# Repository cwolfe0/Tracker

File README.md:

# SHC HAB Tracker
This is the Eagle schematic and board file for the Space Hardware Club HAB tracker.
It is capable of recording GPS, rotation data, pressure and temperature and sending the information via APRS and recording it to an SD card.

The board uses a:
- GPS
- Magnetometer
- MCU
- 5V Regulator
- 3.3V Regulator
- 2 Surefire C123A Batteries in series (6V, 3000mAh)
- APRS-capable Radio
- 2 Logic Gates (for allowing 5V input to the radio from the MCU)
- Pressure Sensor
- Slider Switch
- PDI Interface

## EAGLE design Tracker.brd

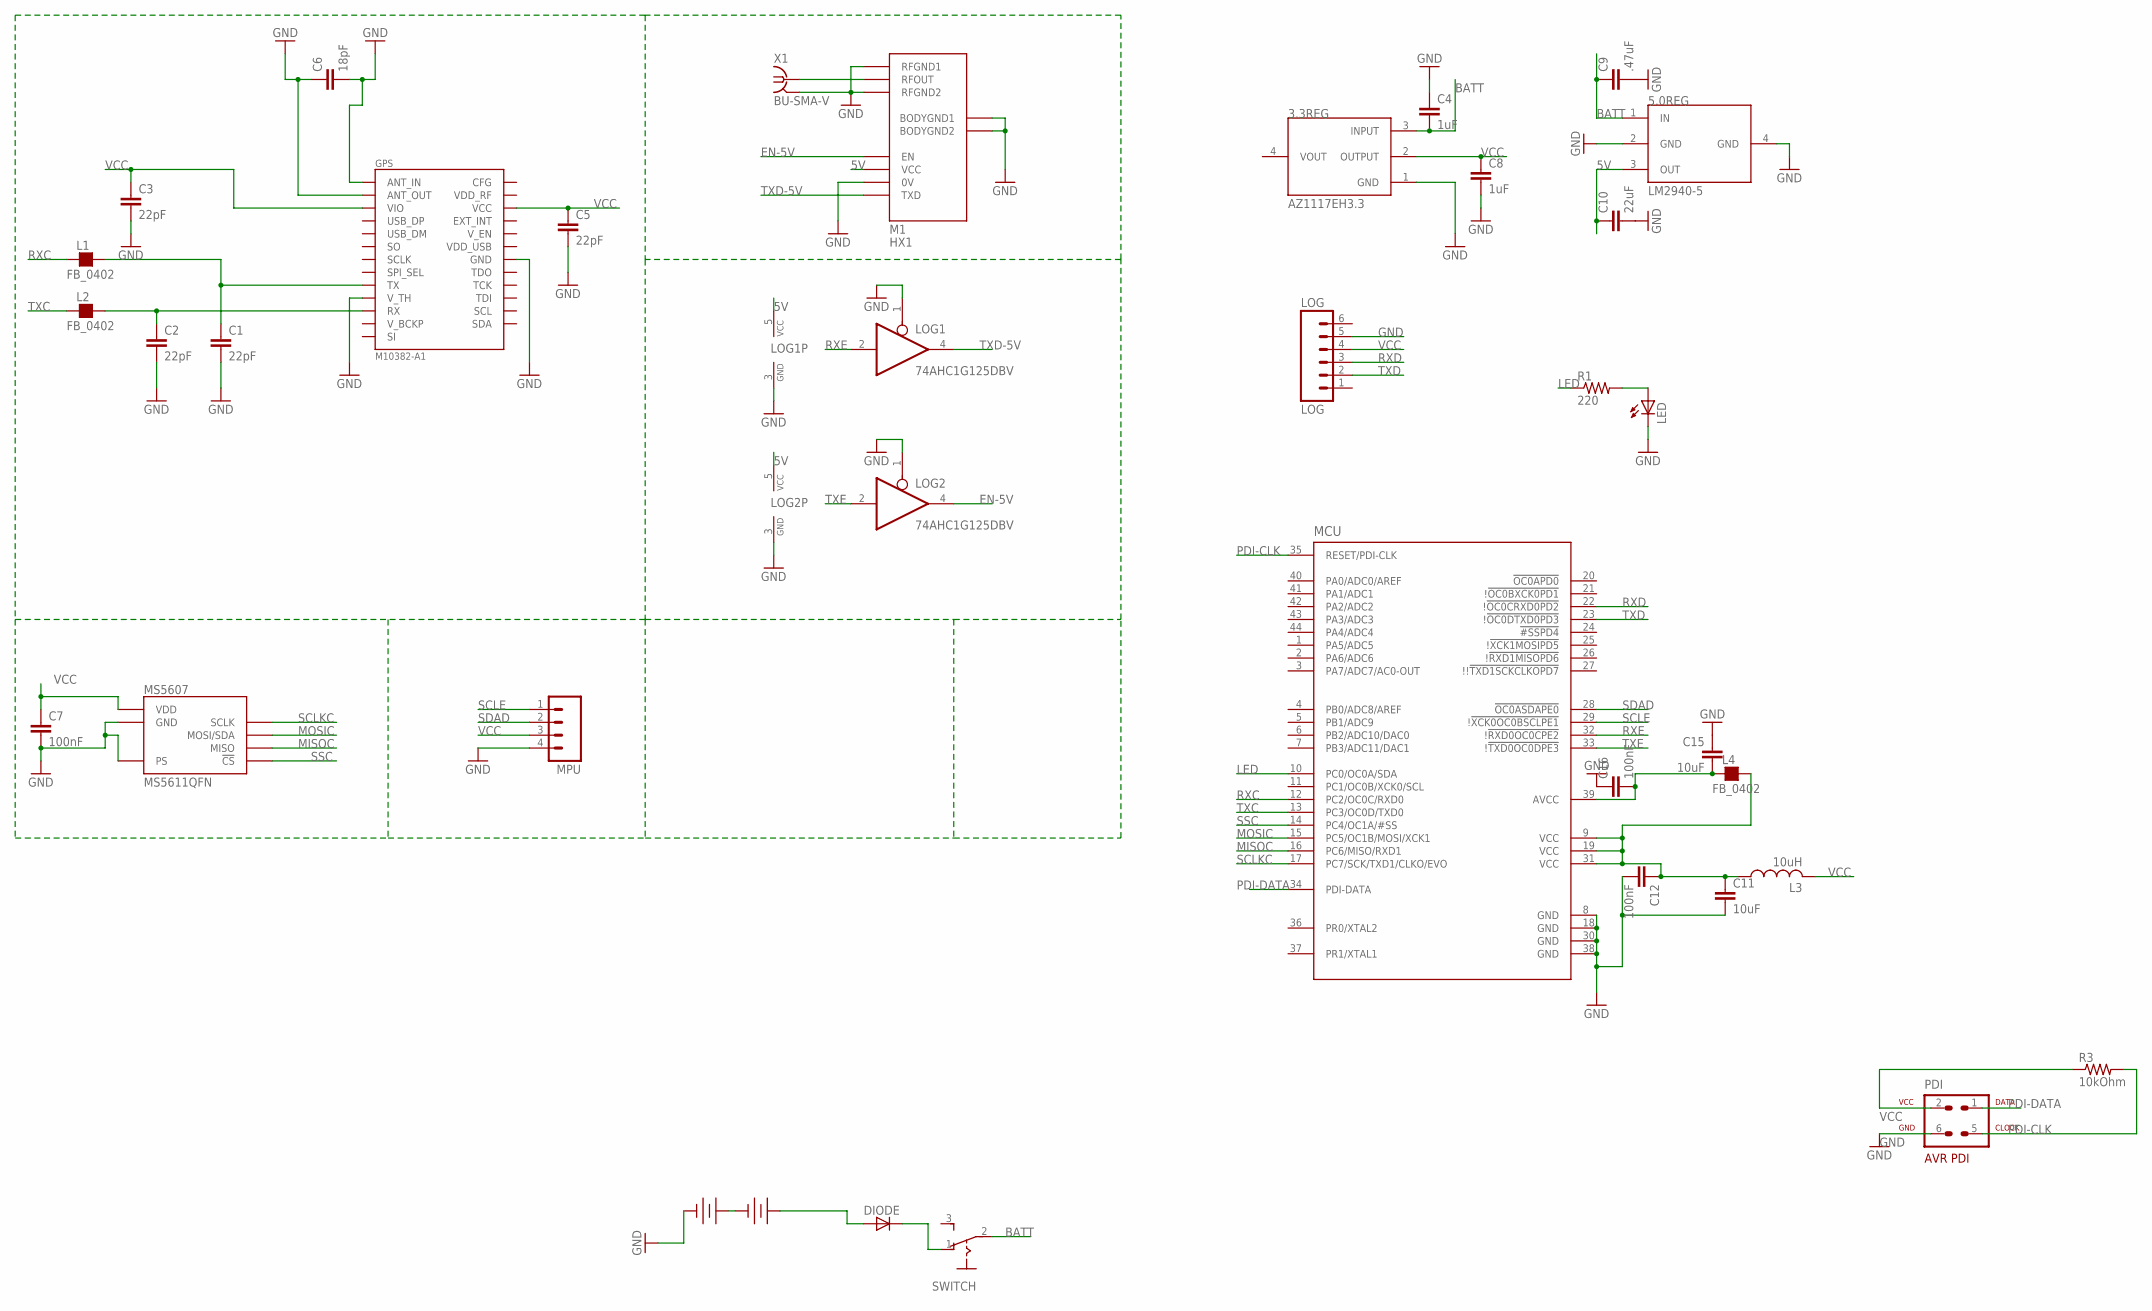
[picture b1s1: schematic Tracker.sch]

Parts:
3.3REG: AZ1117EH3.3; SOT-223
5.0REG: LM2940-5; SOT-223
BATT1, BATT2: 123_BATTERY_HOLDERCR-123-A; CR-123-A_HOLDER
C1, C2, C3, C5: 22pF; 0805
C4, C8: 1uF; 0603-CAP
C6: 18pF; 0805
C7, C12, C16: 100nF; 0805
C9: .47uF; 0603-CAP
C10: 22uF; 0603-CAP
C11, C15: 10uF; 0805
DIODE: LILYPAD-WEARABLES_LED1206; LILYPAD-WEARABLES_LED-1206
GPS: M10382-A1
L1, L2, L4: FB_0402; L0402
L3: 10uH; L2012C
LED: LEDCHIP-LED0603; CHIP-LED0603
LOG: LOG; SPARKFUN_1X06
LOG1, LOG2: 74AHC1G125DBV; SOT23-5
M1: HX1
MCU: AT-XMEGA-XXA4-AU; QFP80P1200X1200X120-44N
MPU: M04; 04P
MS5607: MS5611QFN; MS5611-01BA01
PDI: AVR-7_AVR-PDIVERT; AVR-7_AVR-ISP-6
R1: 220; R0603
R3: 10kOhm; 0805
SWITCH: M251
X1: BU-SMA-V

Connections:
5V: 5.0REG.3 (OUT), C10.1, LOG1.5 (VCC), LOG2.5 (VCC), M1.VCC
AVCC: C15.2, C16.2, L4.1, MCU.39 (AVCC)
BATT: 3.3REG.3 (INPUT), 5.0REG.1 (IN), C4.2, C9.1, SWITCH.2
EN-5V: LOG2.4 (O), M1.EN
GND: 3.3REG.1 (GND), 5.0REG.2 (GND), 5.0REG.4 (GND), BATT2.-, C1.2, C2.2, C3.2, C4.1, C5.2, C6.1, C6.2, C7.2, C8.2, C9.2, C10.2, C11.2, C12.2, C15.1, C16.1, GPS.1 (ANT_IN), GPS.2 (GND), GPS.3 (ANT_OUT), GPS.4 (GND), GPS.12 (V_TH), GPS.14 (GND), GPS.17 (GND), GPS.21 (GND), GPS.24 (GND), GPS.26 (GND), GPS.28 (GND), GPS.33 (GND), GPS.34 (GND), GPS.35 (GND), GPS.36 (GND), LED.C, LOG.5, LOG1.1 (OE), LOG1.3 (GND), LOG2.1 (OE), LOG2.3 (GND), M1.0V, M1.BODYGND1, M1.BODYGND2, M1.RFGND1, M1.RFGND2, MCU.8 (GND), MCU.18 (GND), MCU.30 (GND), MCU.38 (GND), MPU.4, MS5607.2 (PS), MS5607.3 (GND), PDI.6, X1.2 (GND), X1.3 (GND), X1.4 (GND), X1.5 (GND)
LED: MCU.10 (PC0/OC0A/SDA), R1.1
MISOC: MCU.16 (PC6/MISO/RXD1), MS5607.6 (MISO)
MOSIC: MCU.15 (PC5/OC1B/MOSI/XCK1), MS5607.7 (MOSI/SDA)
unnamed: C1.1, GPS.11 (TX), L1.2
unnamed: C2.1, GPS.13 (RX), L2.2
unnamed: BATT1.-, BATT2.+
unnamed: M1.RFOUT, X1.1
unnamed: BATT1.+, DIODE.A
unnamed: DIODE.C, SWITCH.1 (O)
unnamed: LED.A, R1.2
unnamed: C11.1, C12.1, L3.1, L4.2, MCU.9 (VCC), MCU.19 (VCC), MCU.31 (VCC)
PDI-CLK: MCU.35 (RESET/PDI-CLK), PDI.5, R3.2
PDI-DATA: MCU.34 (PDI-DATA), PDI.1
RXC: L1.1, MCU.12 (PC2/OC0C/RXD0)
RXD: LOG.3, MCU.22 (!!OC0CRXD0PD2)
RXE: LOG1.2 (I), MCU.32 (!!RXD0OC0CPE2)
SCLE: MCU.29 (!!XCK0OC0BSCLPE1), MPU.1
SCLKC: MCU.17 (PC7/SCK/TXD1/CLKO/EVO), MS5607.8 (SCLK)
SDAD: MCU.28 (!OC0ASDAPE0), MPU.2
SSC: MCU.14 (PC4/OC1A/#SS), MS5607.4 (!CS!), MS5607.5 (!CS!)
TXC: L2.1, MCU.13 (PC3/OC0D/TXD0)
TXD: LOG.2, MCU.23 (!!OC0DTXD0PD3)
TXD-5V: LOG1.4 (O), M1.TXD
TXE: LOG2.2 (I), MCU.33 (!!TXD0OC0DPE3)
VCC: 3.3REG.2 (OUTPUT), C3.1, C5.1, C7.1, C8.1, GPS.5 (VIO), GPS.27 (VCC), L3.2, LOG.4, MPU.3, MS5607.1 (VDD), PDI.2, R3.1

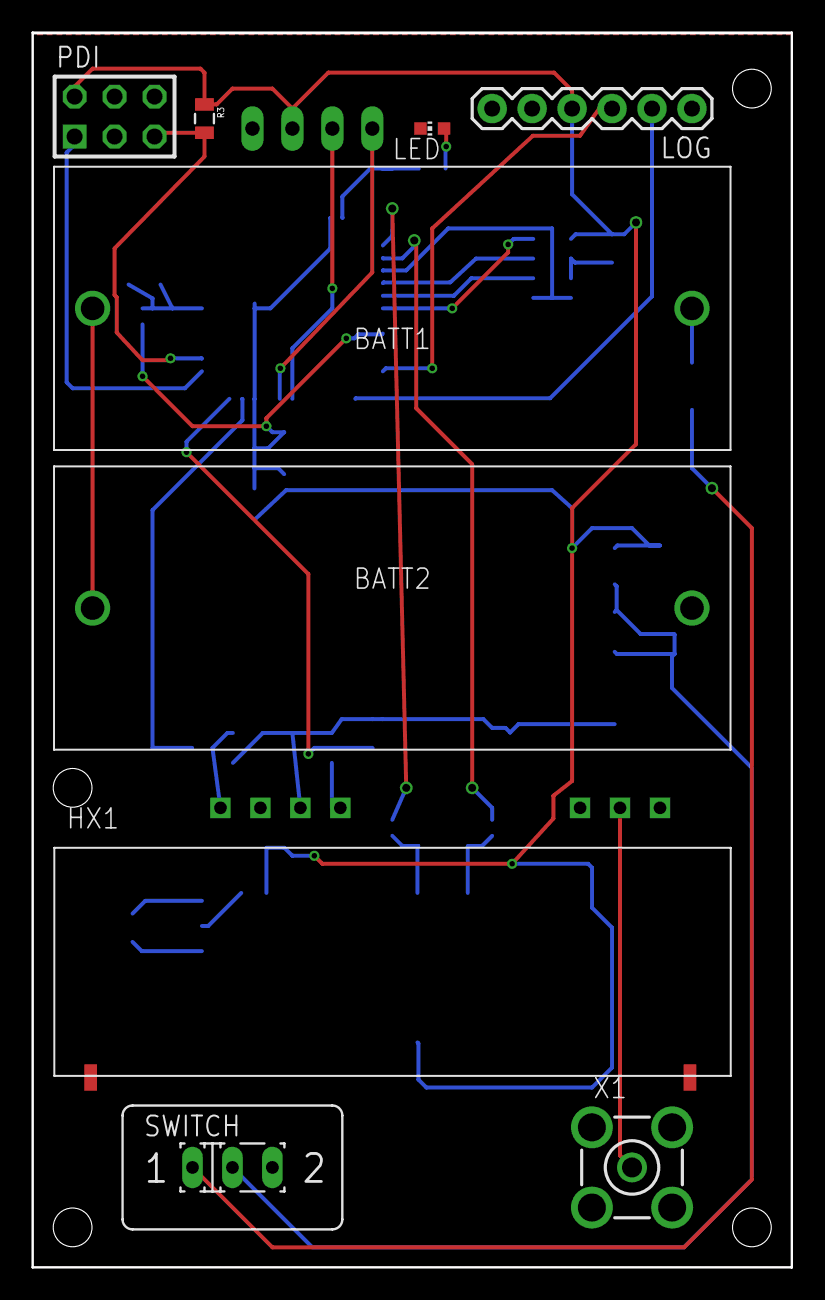
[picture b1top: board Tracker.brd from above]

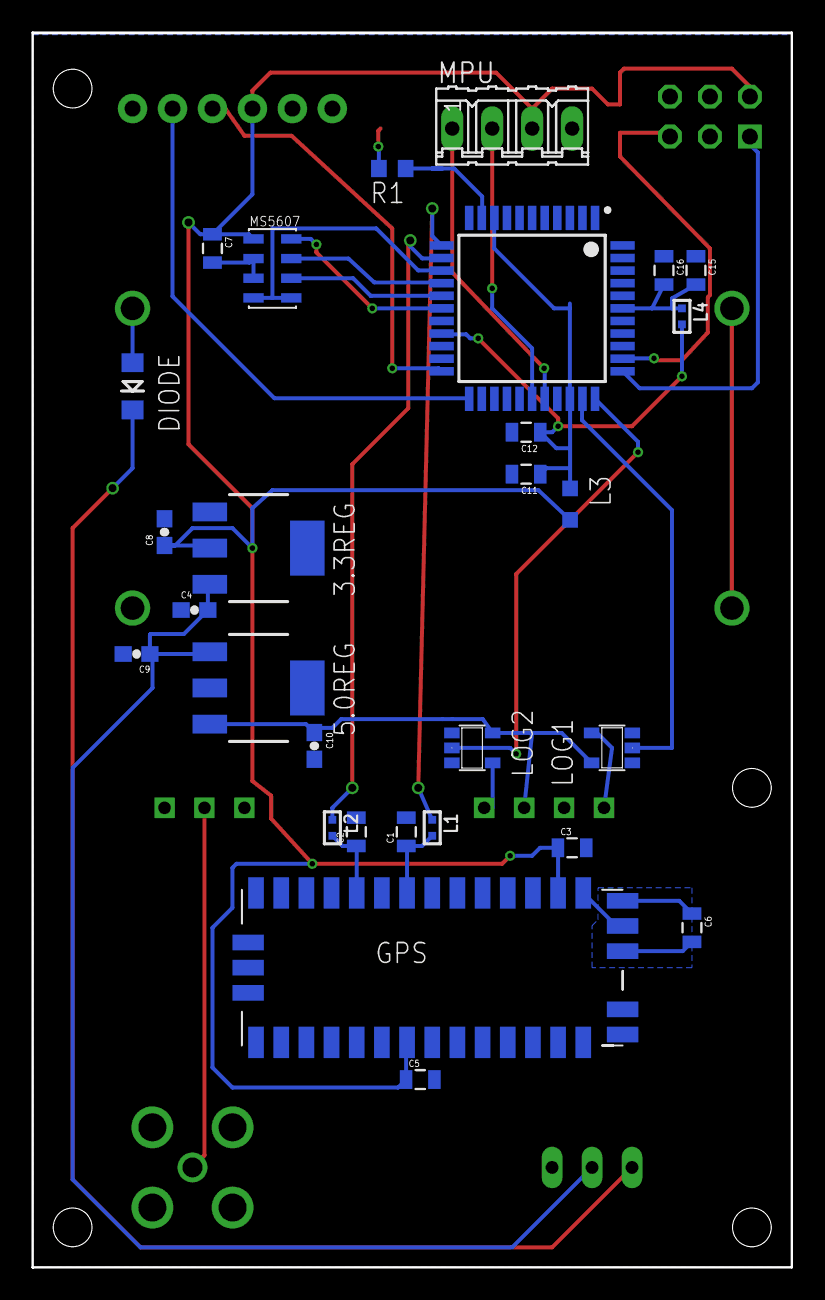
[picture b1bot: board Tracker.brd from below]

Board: 2 copper layers, 48.3 x 78.5 mm, 37 parts (28 on the bottom side), 30 nets.

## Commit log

2017-10-23 rev 1
2017-10-23 rev2
    Removed .x#h files, removed teaching examples, shrunk footprint, made project library
2017-10-23 Update Readme, add GERBER
    Change Readme to be more representative of the tracker instead of Physoon, add SeedFusion CAM files, remove errant EAGLE files
2017-10-23 DRILL KILL
    added drills, sorry for bad commit summary

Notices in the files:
parts and their libraries:
SparkFun: Licensing: CC v3.0 Share-Alike You are welcome to use this library for commercial purposes.
rc-master-smd: Copyright (C) 2007, Bob Starr
